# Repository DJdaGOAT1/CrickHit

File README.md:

# CrickHit
### An Embedded Real-Time Cricket Game on the TI MSPM0G3507

---

## Project Overview

CrickHit is a real-time cricket batting game built from scratch on the **TI MSPM0G3507 LaunchPad** with a **ST7735R 128x160 TFT LCD**. The player controls a batsman using a slide potentiometer and physical switches to hit balls bowled with realistic curve trajectories. The game runs entirely on bare-metal interrupts with no RTOS, using fixed-point physics, sprite compositing, a custom 5-bit binary-weighted DAC for audio, and multilingual UI support.

Developed as the final project for **ECE 319H: Introduction to Embedded Systems (Honors)** at **The University of Texas at Austin**, Spring 2026.

**Authors:** Devansh Joshi and Calum Cheah

---

## Gameplay / Demo

A top-down cricket scene is rendered on the LCD. A bowler at the top of the screen delivers balls toward the stumps at the bottom. The player moves the batsman horizontally with a slide potentiometer and triggers left or right bat swings using physical switches.

A demo of CrickHit is available [here](https://youtu.be/25Vt4UJRmN4):

### Scoring

Runs are awarded based on how precisely the bat contacts the ball:

| Result | Condition | Runs |
|---|---|---|
| Perfect Hit | Ball within 3px of ideal contact point | +6 |
| Good Hit | Ball within 8px of ideal contact point | +4 |
| Hit | Ball within 14px of ideal contact point | +2 |
| Wide | Ball delivered too far from the batsman | +1 |
| Wicket (OUT) | Ball hits the stumps without being hit | Score resets |

Swinging on the correct side (left swing for balls approaching from the left, right swing for the right) gives a threshold bonus. Swinging on the wrong side applies a 2px penalty to all scoring thresholds, making it harder to score high.

### Ball Physics

Each delivery uses kinematic equations with 6-bit fixed-point arithmetic for sub-pixel precision:
- Initial horizontal velocity is randomized
- A curve acceleration (`ax`) is computed so the ball arcs toward the stumps
- Target position uses a Gaussian random distribution (Central Limit Theorem approximation) so slower deliveries aim more accurately at the stumps while faster ones scatter wider
- Speed-proportional jitter is added to the scoring calculation to prevent quantization lockout at high speeds, where the large step size would otherwise restrict the ball to only a few Y positions in the hit zone

### Wide Detection

A ball is called wide if it passes the batsman's reach without being hit:
- **Off-wide:** Ball passes more than 15px past the batsman's right edge
- **Leg-wide:** Ball is left of the pitch with a gap greater than 3px from the batsman's left edge

If a wide ball subsequently hits the stumps or gets hit by the bat, the wide run is revoked.

### Game Controls

| Input | Action |
|---|---|
| Slide potentiometer | Move batsman left/right |
| LEFT switch (PA25) | Swing bat to the left |
| RIGHT switch (PA27) | Swing bat to the right |
| TOP switch (PA24) | Increase ball delivery speed |
| BOTTOM switch (PA26) | Decrease ball delivery speed |
| TOP + BOTTOM | Return to home screen |
| LEFT + RIGHT | Pause / unpause |
| S1 (LaunchPad) | Enable speaker |
| S2 (LaunchPad) | Disable speaker |

A 1500ms cooldown is enforced between swings to prevent spam.

---

## Hardware

### Platform
- **MCU:** TI MSPM0G3507 LaunchPad (ARM Cortex-M0+, 80 MHz)
- **Display:** ST7735R 128x160 TFT LCD over SPI

### Pin Assignments

| Peripheral | Pin(s) | Function |
|---|---|---|
| SPI1 SCLK | PB9 | LCD clock |
| SPI1 CS | PB6 | LCD chip select |
| SPI1 MOSI | PB8 | LCD data |
| LCD Reset | PB15 | ST7735 !RST |
| LCD D/C | PA13 | ST7735 RS (Data/Command) |
| Slide Pot | PB18 (ADC1 Ch5) | Batsman horizontal position |
| 5-bit DAC | PB0-PB4 | Binary-weighted audio output |
| Speaker Enable | PB12 | Active-low speaker control |
| TOP Switch | PA24 | Increase ball speed |
| LEFT Switch | PA25 | Left bat swing |
| BOTTOM Switch | PA26 | Decrease ball speed |
| RIGHT Switch | PA27 | Right bat swing |
| LED 0 | PA15 | 2-run hit indicator |
| LED 1 | PA16 | 4-run hit indicator |
| LED 2 | PA17 | 6-run hit indicator |

### Required Components
- MSPM0G3507 LaunchPad
- ST7735R 128x160 TFT LCD
- Slide potentiometer
- 4 momentary push switches
- 5-bit binary-weighted DAC
- Speaker with enable circuit
- 3 LEDs with current-limiting resistors

### Custom PCB

We designed a custom PCB in KiCad that consolidates all of the hardware circuitry onto a single board. The PCB integrates the ST7735R LCD connector, the 5-bit binary-weighted DAC, the speaker amplifier circuit (MCP34119P), all four game switches, the slide potentiometer input, LED indicators, IR receiver (TSOP31438), a ULN2003B Darlington driver, UART debugging header, and TExaS connector -- all routed to the MSPM0G3507 LaunchPad. This eliminates the need for breadboard wiring and makes the entire system compact and reliable.

### 3D-Printed Enclosure

A custom controller-style enclosure was designed in **Autodesk Fusion** to house the PCB and LaunchPad together as a handheld game controller.

An STL of the enclosure is included in the `3D_Enclosure/`

---

## Software Architecture

### Interrupt-Driven Design

The entire game runs on three interrupt sources with no polling loops in the main thread:

| ISR | Source | Rate | Purpose |
|---|---|---|---|
| `TIMG12_IRQHandler` | TimerG12 | 30 Hz | Main game tick: polls ADC, updates all sprite positions, runs collision detection, sets render flag |
| `TIMG0_IRQHandler` | TimerG0 | 1 kHz | Swing cooldown timer (counts up to 1500ms between allowed swings) |
| SysTick | SysTick | 11 kHz | Streams audio samples through the 5-bit DAC |

The main loop blocks on a flag set by the 30 Hz ISR, then handles rendering, UI updates, and screen transitions. All ST7735 drawing occurs in main context only, never inside an ISR.

### Object-Oriented Sprite System

A `Sprite` base class provides position tracking, dirty-flag rendering, overlap detection, and background-aware erasure. Four derived classes implement the game objects:

**Ball** -- Fixed-point position (`fx`, `fy`) and velocity (`vx`, `vy`) with curve acceleration (`ax`). A 5-state machine drives the lifecycle:
```
IDLE --> BOWLING --> HIT_LEFT/HIT_RIGHT --> RESET --> IDLE
                 \-> (stump collision) --> RESET --> IDLE
```

**Batsman** -- Position mapped from the slide potentiometer ADC reading (calibrated range 1587-192). Left swing has 8 animation frames, right swing has 10. The current frame pointer is updated each game tick during a swing.

**Bowler** -- Cycles through 7 animation frames. Frame 4 is the release frame, which triggers ball delivery with randomized trajectory parameters.

**Stump** -- Two frames (intact and broken). On wicket, the broken frame displays for 30 game ticks (~1 second) before the OUT screen appears.

### Rendering Pipeline

The `Renderer` module composites sprites against the pitch background to prevent texture artifacts:

1. For each pixel in a sprite, check if it's transparent (`BG_COLOR = 0x9772`)
2. If transparent, fetch the corresponding pixel from the pitch bitmap (or outfield green if outside the pitch bounds)
3. White crease pixels in the pitch are substituted with pitch surface color to avoid visual bleed
4. The composed buffer is written as a single SPI transaction for flicker-free output

`EraseToBackground()` restores the pitch texture when a sprite moves, handling the partial-width erase case when the batsman slides left or right.

### Audio System

Three sound effects are stored as raw sample arrays and played through a 5-bit binary-weighted DAC at 11 kHz via SysTick:

| Sound | Samples | Trigger |
|---|---|---|
| IPL Stadium | 28,179 | Title screen crowd atmosphere |
| Bat Hit | 2,239 | Ball contacts bat |
| Stump Hit | 3,592 | Ball hits stumps (wicket) |

The speaker can be muted/unmuted at runtime via the LaunchPad S1/S2 buttons, controlled through GPIO PB12.

### Internationalization

The game supports **English** and **Spanish**, selectable on the home screen:
- TOP switch selects English, BOTTOM switch selects Spanish
- All UI strings ("Score"/"Puntaje", "Wide"/"Ancha", instruction text) are stored in a `Phrases[][]` lookup table
- A Devanagari (Hindi) font renderer (`HindiFont.h/cpp`) with 31 glyphs and diacritic support is included for future localization

---

## Project Structure

```
CrickHit/
|-- README.md
|-- LICENSE
|-- mspm0g3507.cmd                 Linker script
|
|-- src/                           Game source code
|   |-- Lab9HMain.cpp              Main game loop, ISRs, collision detection, game state
|   |-- GameDefs.h                 All constants: sprite dimensions, physics params, thresholds
|   |-- Sprites.h                  Sprite class hierarchy (Sprite, Ball, Batsman, Bowler, Stump)
|   |-- Sprite.cpp                 Base class: draw, erase, overlap detection
|   |-- Ball.cpp                   Fixed-point kinematics, trajectory, state machine
|   |-- Batsman.cpp                Potentiometer input mapping, swing animation
|   |-- Bowler.cpp                 Bowling animation, release frame detection
|   |-- Stump.cpp                  Intact/broken state, hit animation
|   |-- Renderer.h / .cpp          Background-compositing sprite renderer
|   |-- Screens.h / .cpp           Home, instruction, pause, and OUT screens + i18n
|   |-- Sound.h / .cpp             DAC audio playback (SysTick-driven)
|   |-- LED.h / .cpp               Hit-quality LED indicators
|   |-- Switch.h / .cpp            4-switch input reading
|   |-- SmallFont.h / .cpp         Numeric score display font
|   +-- HindiFont.h / .cpp         Devanagari script renderer (31 glyphs, 12x16px)
|
|-- inc/                           Hardware abstraction libraries (see Acknowledgments)
|   |-- Clock.h / .cpp             System clock configuration (80 MHz PLL)
|   |-- DAC5.h / .cpp              5-bit DAC GPIO driver
|   |-- LaunchPad.h / .cpp         LaunchPad GPIO and button initialization
|   |-- SPI.h / .cpp               SPI communication driver
|   |-- ST7735.h / .cpp            ST7735 LCD driver (drawing, text, bitmaps)
|   |-- SlidePot.h / .cpp          Slide potentiometer ADC driver
|   |-- TExaS.h / .cpp             TExaS grading and logic analyzer system
|   |-- Timer.h / .cpp             Hardware timer configuration and arming
|   |-- SysTick.s                  SysTick assembly routines
|   +-- msp.s                      MSP device assembly support
|
|-- images/                        Sprite assets
|   |-- images.h                   All sprite bitmap data as C arrays (RGB565, 16-bit)
|   |-- ball/                      Ball sprite source BMP
|   |-- batsman/                   Batsman idle + 7 swing frame BMPs
|   |-- bowler/                    7 bowling animation frame BMPs
|   |-- stump/                     Intact and broken stump BMPs
|   |-- pitch/                     35x140 pitch surface bitmap
|   +-- BmpConvert16.exe           BMP-to-RGB565 C array converter
|
|-- sounds/                        Audio assets
|   |-- sounds.h                   Audio sample arrays
|   |-- ipl_stadium.wav            Title screen crowd audio
|   |-- bat_hit.wav                Bat contact sound effect
|   +-- stump.wav                  Wicket sound effect
|
|-- PCB_Design/                    KiCad project for the custom game PCB
|   |-- CrickHit_PCB.kicad_sch    Schematic
|   |-- CrickHit_PCB.kicad_pcb    PCB layout
|   |-- CrickHit_PCB.kicad_pro    Project file
|   |-- utece.kicad_sym            Custom symbol library
|   +-- logo.bmp                   Board silkscreen logo
|
|-- 3D_Enclosure/                  STL file for the controller enclosure
|   +-- Enclosure.stl
|
|-- tools/                         Development utilities
|   |-- curve.py                   Ball trajectory simulation for tuning physics
|   +-- flood_fill_sprites.py      Sprite transparency preprocessing
|
|-- ticlang/
|   +-- startup_mspm0g3507_ticlang.c   MCU startup and vector table
|
+-- targetConfigs/
    +-- MSPM0G3507.ccxml           Debug target configuration
```

---

## Building and Flashing

### Prerequisites
- **Code Composer Studio (CCS)** with the TI CLANG compiler (v4.0+)
- **MSPM0 SDK** (v2.9+)
- MSPM0G3507 LaunchPad with hardware wired per the pin assignments above

### Setup
1. Clone this repository into your CCS workspace
2. **File > Import > CCS Projects**, point to the cloned folder
3. Ensure the MSPM0 SDK is installed and `COM_TI_MSPM0_SDK_INSTALL_DIR` is set
4. Build the project -- the `inc/` folder contains all necessary driver libraries, so no external ValvanoWare dependency is needed
5. Connect the LaunchPad via USB and flash

The `inc/` directory contains the hardware abstraction libraries that originally lived in a shared `MSPM0_ValvanoWare/inc/` directory. Include paths have been updated so this project builds standalone.

---

## Development Utilities

**`curve.py`** -- Python script that simulates ball trajectories with the same kinematic equations used in the game. Plots predicted paths for tuning physics constants (velocity, acceleration, target variance) without reflashing the board.

**`flood_fill_sprites.py`** -- Post-processes `images.h` after BMP-to-C conversion. Flood-fills exterior background pixels with the transparent color (`0x9772`) while preserving interior white pixels (bat highlights, ball shine, etc.) that should not be treated as transparent during compositing.

---

## Acknowledgments

This project was built for **ECE 319H: Introduction to Embedded Systems (Honors)** at **The University of Texas at Austin**, taught by **Professor Ramesh Yerraballi**. Thank you to Dr. Yerraballi, Dr. Valvano, Dr. Chin, Dr. Holt, and the ECE319 TAs for their instruction and support throughout ECE319H!

The hardware abstraction libraries in the `inc/` directory -- Clock, DAC5, LaunchPad, SPI, ST7735, SlidePot, TExaS, and Timer -- were written by **Jonathan Valvano** as part of the [MSPM0 ValvanoWare](http://users.ece.utexas.edu/~valvano/) curriculum framework. These drivers provide the foundational embedded systems infrastructure (clock configuration, SPI communication, LCD rendering, ADC interfacing, timer management) that CrickHit is built on.

---

## Authors

**Devansh Joshi** -- [GitHub](https://github.com/devanshjoshi08)  
**Calum Cheah** -- [GitHub](https://github.com/CalumCheah)

---

## License

This project is licensed under the [MIT License](LICENSE).

The hardware abstraction libraries in `inc/` are provided by Jonathan Valvano and Texas Instruments under their own respective terms and are not covered by the MIT License.

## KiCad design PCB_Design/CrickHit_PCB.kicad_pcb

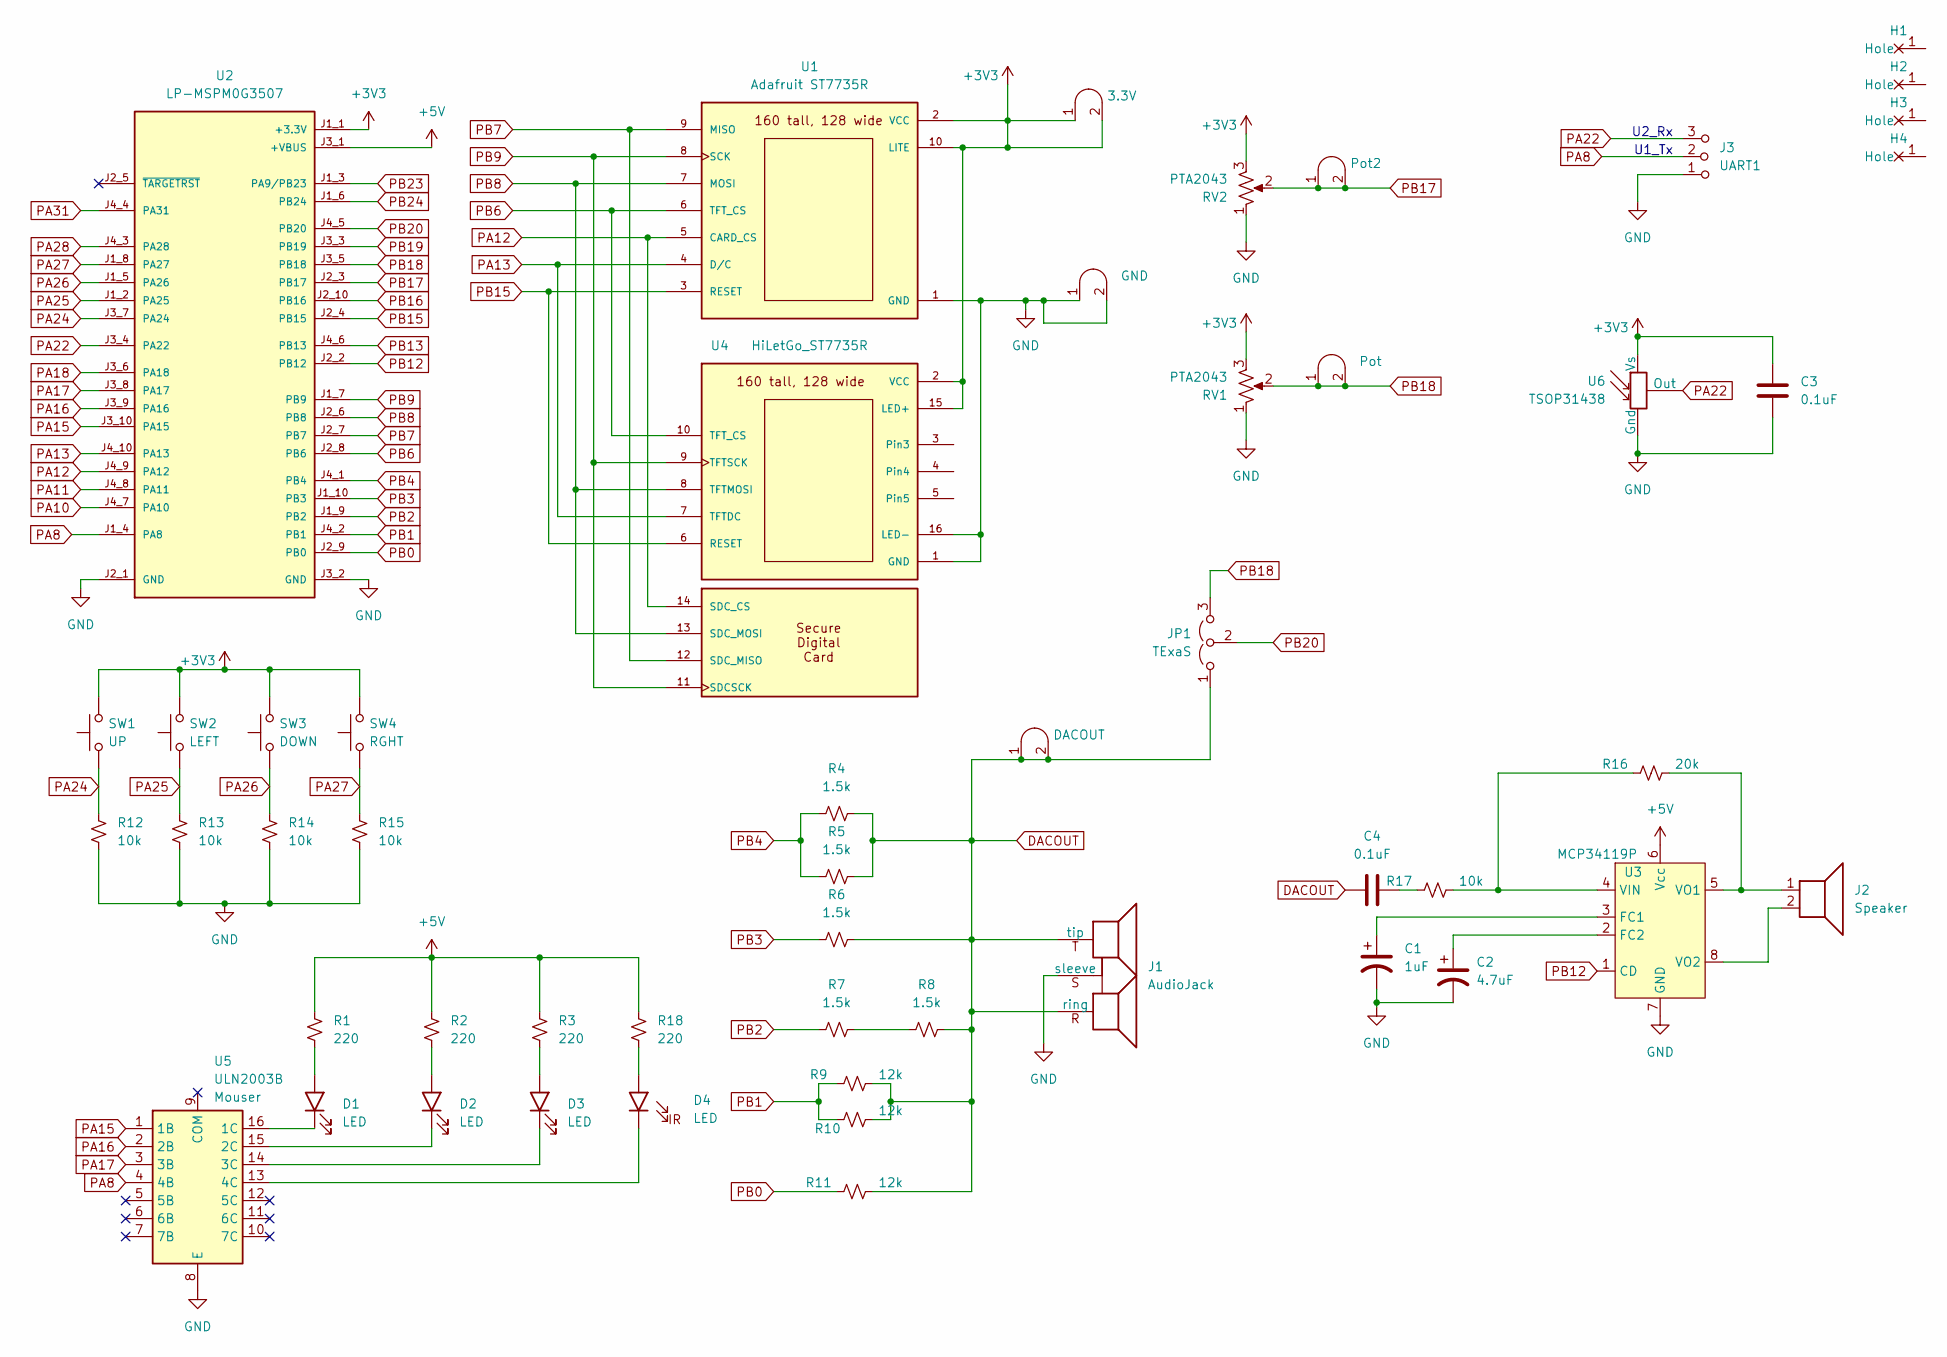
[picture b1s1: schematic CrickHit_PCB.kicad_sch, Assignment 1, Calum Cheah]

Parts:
C1: 1uF; CP_Radial_Tantal200mil
C2: 4.7uF; CP_Radial_Tantal200mil
C3, C4: 0.1uF; C_Axial_200mil
D1, D2, D3, D4: LED; LED_D5.0mm
H1, H2, H3, H4: MountingHole_4_40
J1: AudioJack; Jack_3.5mm_CUI_SJ1-3523N_Horizontal
J2: Speaker; PinHeader_1x02_P2.54mm_Vertical
J3: UART1; PinHeader_1x03_P2.54mm_Vertical
J4: Pot; Testpoint_1x02_P2.54mm
J5: Pot2; Testpoint_1x02_P2.54mm
J6: GND; Testpoint_1x02_P2.54mm
J7: DACOUT; Testpoint_1x02_P2.54mm
JP1: TExaS; PinHeader_1x03_P2.54mm_Vertical
R1, R2, R3, R18: 220; R_Axial_DIN0204_L3.6mm_D1.6mm_P7.62mm_Horizontal
R4, R5, R6, R7, R8: 1.5k; R_Axial_DIN0204_L3.6mm_D1.6mm_P7.62mm_Horizontal
R9, R10, R11: 12k; R_Axial_DIN0204_L3.6mm_D1.6mm_P7.62mm_Horizontal
R12, R13, R14, R15, R17: 10k; R_Axial_DIN0204_L3.6mm_D1.6mm_P7.62mm_Horizontal
R16: 20k; R_Axial_DIN0204_L3.6mm_D1.6mm_P7.62mm_Horizontal
RV1, RV2: PTA2043; PTA2043pot
SW1: UP; SW_PUSH_6mm
SW2: LEFT; SW_PUSH_6mm
SW3: DOWN; SW_PUSH_6mm
SW4: RGHT; SW_PUSH_6mm
TP1: 3.3V; Testpoint_1x02_P2.54mm
U1: Adafruit ST7735R; adafruit_st7735r
U2: LP-MSPM0G3507; ti_LP_MSPM0G3507
U3: MCP34119P; DIP-8_W7.62mm_LongPads
U4: HiLetGo_ST7735R; hiletgo_st7735r
U5: ULN2003B; DIP-16_W7.62mm
U6: TSOP31438

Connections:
+3V3: C3.2, RV1.3, RV2.3, SW1.2, SW2.2, SW3.2, SW4.2, TP1.1 (A), TP1.2 (B), U1.2 (VCC), U1.10 (LITE), U2.J1_1 (+3.3V), U4.2 (VCC), U4.15 (LED+), U6.2 (Vs)
+5V: R1.1, R2.1, R3.1, R18.1, U2.J3_1 (+VBUS), U3.6 (Vcc)
DACOUT: C4.2, J1.R (ring), J1.T (tip), J7.1 (A), J7.2 (B), JP1.1 (A), R4.1, R5.1, R6.1, R8.1, R9.1, R10.1, R11.1
GND: C1.2, C2.2, C3.1, J1.S (sleeve), J3.1 (A), J6.1 (A), J6.2 (B), R12.2, R13.2, R14.2, R15.2, RV1.1, RV2.1, U1.1 (GND), U2.J2_1 (GND), U2.J3_2 (GND), U3.7 (GND), U4.1 (GND), U4.16 (LED-), U5.8 (E), U6.1 (Gnd)
unnamed: C4.1, R17.2
unnamed: D1.2 (A), R1.2
unnamed: D1.1 (K), U5.16 (1C)
unnamed: D2.2 (A), R2.2
unnamed: D2.1 (K), U5.15 (2C)
unnamed: D3.2 (A), R3.2
unnamed: D3.1 (K), U5.14 (3C)
unnamed: D4.2 (A), R18.2
unnamed: D4.1 (K), U5.13 (4C)
unnamed: R7.1, R8.2
unnamed: C1.1, U3.3 (FC1)
unnamed: C2.1, U3.2 (FC2)
unnamed: R16.2, R17.1, U3.4 (VIN)
unnamed: J2.1, R16.1, U3.5 (VO1)
unnamed: J2.2, U3.8 (VO2)
PA8: J3.2 (B), U2.J1_4 (PA8), U5.4 (4B)
PA10: U2.J4_7 (PA10)
PA11: U2.J4_8 (PA11)
PA12: U1.5 (CARD_CS), U2.J4_9 (PA12), U4.14 (SDC_CS)
PA13: U1.4 (D/C), U2.J4_10 (PA13), U4.7 (TFTDC)
PA15: U2.J3_10 (PA15), U5.1 (1B)
PA16: U2.J3_9 (PA16), U5.2 (2B)
PA17: U2.J3_8 (PA17), U5.3 (3B)
PA18: U2.J3_6 (PA18)
PA22: J3.3 (C), U2.J3_4 (PA22), U6.3 (Out)
PA24: R12.1, SW1.1, U2.J3_7 (PA24)
PA25: R13.1, SW2.1, U2.J1_2 (PA25)
PA26: R14.1, SW3.1, U2.J1_5 (PA26)
PA27: R15.1, SW4.1, U2.J1_8 (PA27)
PA28: U2.J4_3 (PA28)
PA31: U2.J4_4 (PA31)
PB0: R11.2, U2.J2_9 (PB0)
PB1: R9.2, R10.2, U2.J4_2 (PB1)
PB2: R7.2, U2.J1_9 (PB2)
PB3: R6.2, U2.J1_10 (PB3)
PB4: R4.2, R5.2, U2.J4_1 (PB4)
PB6: U1.6 (TFT_CS), U2.J2_8 (PB6), U4.10 (TFT_CS)
PB7: U1.9 (MISO), U2.J2_7 (PB7), U4.12 (SDC_MISO)
PB8: U1.7 (MOSI), U2.J2_6 (PB8), U4.8 (TFTMOSI), U4.13 (SDC_MOSI)
PB9: U1.8 (SCK), U2.J1_7 (PB9), U4.9 (TFTSCK), U4.11 (SDCSCK)
PB12: U2.J2_2 (PB12), U3.1 (CD)
PB13: U2.J4_6 (PB13)
PB15: U1.3 (RESET), U2.J2_4 (PB15), U4.6 (RESET)
PB16: U2.J2_10 (PB16)
PB17: J5.1 (A), J5.2 (B), RV2.2, U2.J2_3 (PB17)
PB18: J4.1 (A), J4.2 (B), JP1.3 (B), RV1.2, U2.J3_5 (PB18)
PB19: U2.J3_3 (PB19)
PB20: JP1.2 (C), U2.J4_5 (PB20)
PB23: U2.J1_3 (PA9/PB23)
PB24: U2.J1_6 (PB24)

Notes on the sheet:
U2_Rx
U1_Tx

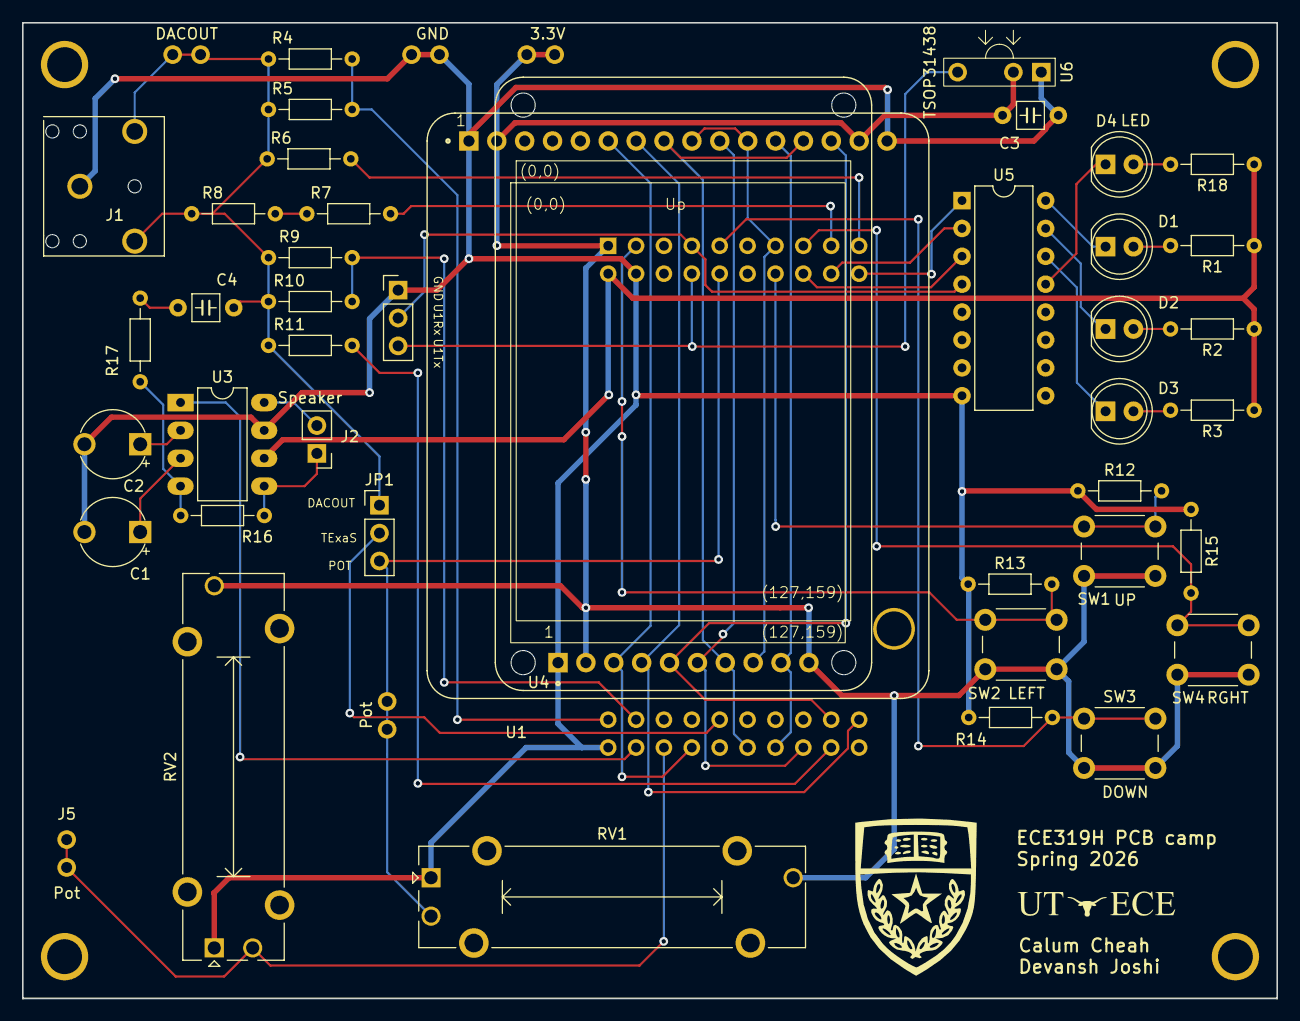
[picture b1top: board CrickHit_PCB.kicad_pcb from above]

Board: 2 copper layers, 114.3 x 88.9 mm, 51 parts (1 on the bottom side), 44 nets.

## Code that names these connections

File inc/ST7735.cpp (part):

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// ST7735
// Backlight (pin 10)     to +3.3 V
// MISO (pin 9) (NC)
// SCK (pin 8)            to SPI1 SCLK: PB9
// MOSI (pin 7)           to SPI1 PICO: PB8
// TFT_CS (pin 6)         to SPI1 CS0:  PB6
// CARD_CS (pin 5) (NC)
// Data/Command (pin 4)   to PA13 (GPIO), high for data, low for command
// RESET (pin 3)          to PB15 (GPIO)
// VCC (pin 2)            to +3.3 V
// Gnd (pin 1)            to ground

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// Silkscreen Label (SDC side up; LCD side down) - Connection
// VCC  - +3.3 V
// GND  - Ground
// !SCL - SPI1 SCLK: PB9 clock
// !SDA - SPI1 PICO: PB8 MOSI SPI data from microcontroller to TFT or SDC
// DC   - GPIO       PA13 TFT data/command
// RES  - GPIO       PB15 TFT reset
// CS   - SPI1 CS0:  PB6 TFT_CS, active low to enable TFT
// *CS  - (NC) SDC_CS, active low to enable SDC
// MISO - (NC) MISO SPI data from SDC to microcontroller
// SDA  - (NC) I2C data for ADXL345 accelerometer
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// Silkscreen Label (SDC side up; LCD side down) - Connection
// VCC  - +3.3 V
// GND  - Ground
// !SCL - SPI1 SCLK: PB9
// !SDA - SPI1 PICO: PB8 MOSI SPI data from microcontroller to TFT or SDC
// DC   - GPIO       PA13 TFT data/command
// RES  - GPIO       PB15 TFT reset
// CS   - SPI1 CS0:  PB6 TFT_CS, active low to enable TFT
// *CS  - (NC) SDC_CS, active low to enable SDC
// MISO - (NC) MISO SPI data from SDC to microcontroller
// X- (NC) analog input X-axis from ADXL335 accelerometer
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// MOSI   (pin 13) SDC, to MOSI
// MISO   (pin 12) SDC, to MISO
// SCK    (pin 11) SDC, to serial clock
// CS     (pin 10) TFT, to PB6  SPI1 CS0
// SCL    (pin 9)  TFT, to PB9  SPI1 SCLK
// SDA    (pin 8)  TFT, to PB8  MOSI SPI1 PICO
// A0     (pin 7)  TFT, to PA13 Data/Command, high for data, low for command
// RESET  (pin 6)  TFT, to PB15 reset (GPIO), low to reset
// NC     (pins 3,4,5)
// VCC    (pin 2)       to +3.3 V
// GND    (pin 1)       to ground
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// Tyenaza Tyenazaqhf72mi9s3
// ST7735
// LED (pin 8)              to +3.3 V
// SCK (pin 7) SCLK         to PB9 SPI1 SCLK
// SDA (pin 6) MOSI,        to PB8 SPI1 PICO
// A0  (pin 5) Data/Command to PA13 (GPIO), high for data, low for command
// RESET (pin 4)            to PB15 (GPIO), low to reset
// CS  (pin 3)              to PB6 SPI1 CS0:
// Gnd (pin 2)              to ground
// VCC (pin 1)              to +3.3 V

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
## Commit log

2026-05-11 Final Changes
2026-05-11 Added stl of enclosure

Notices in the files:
inc/ST7735.cpp:
MIT license, all text above must be included in any redistribution
Copyright 2026 by Jonathan W. Valvano, valvano@mail.utexas.edu
